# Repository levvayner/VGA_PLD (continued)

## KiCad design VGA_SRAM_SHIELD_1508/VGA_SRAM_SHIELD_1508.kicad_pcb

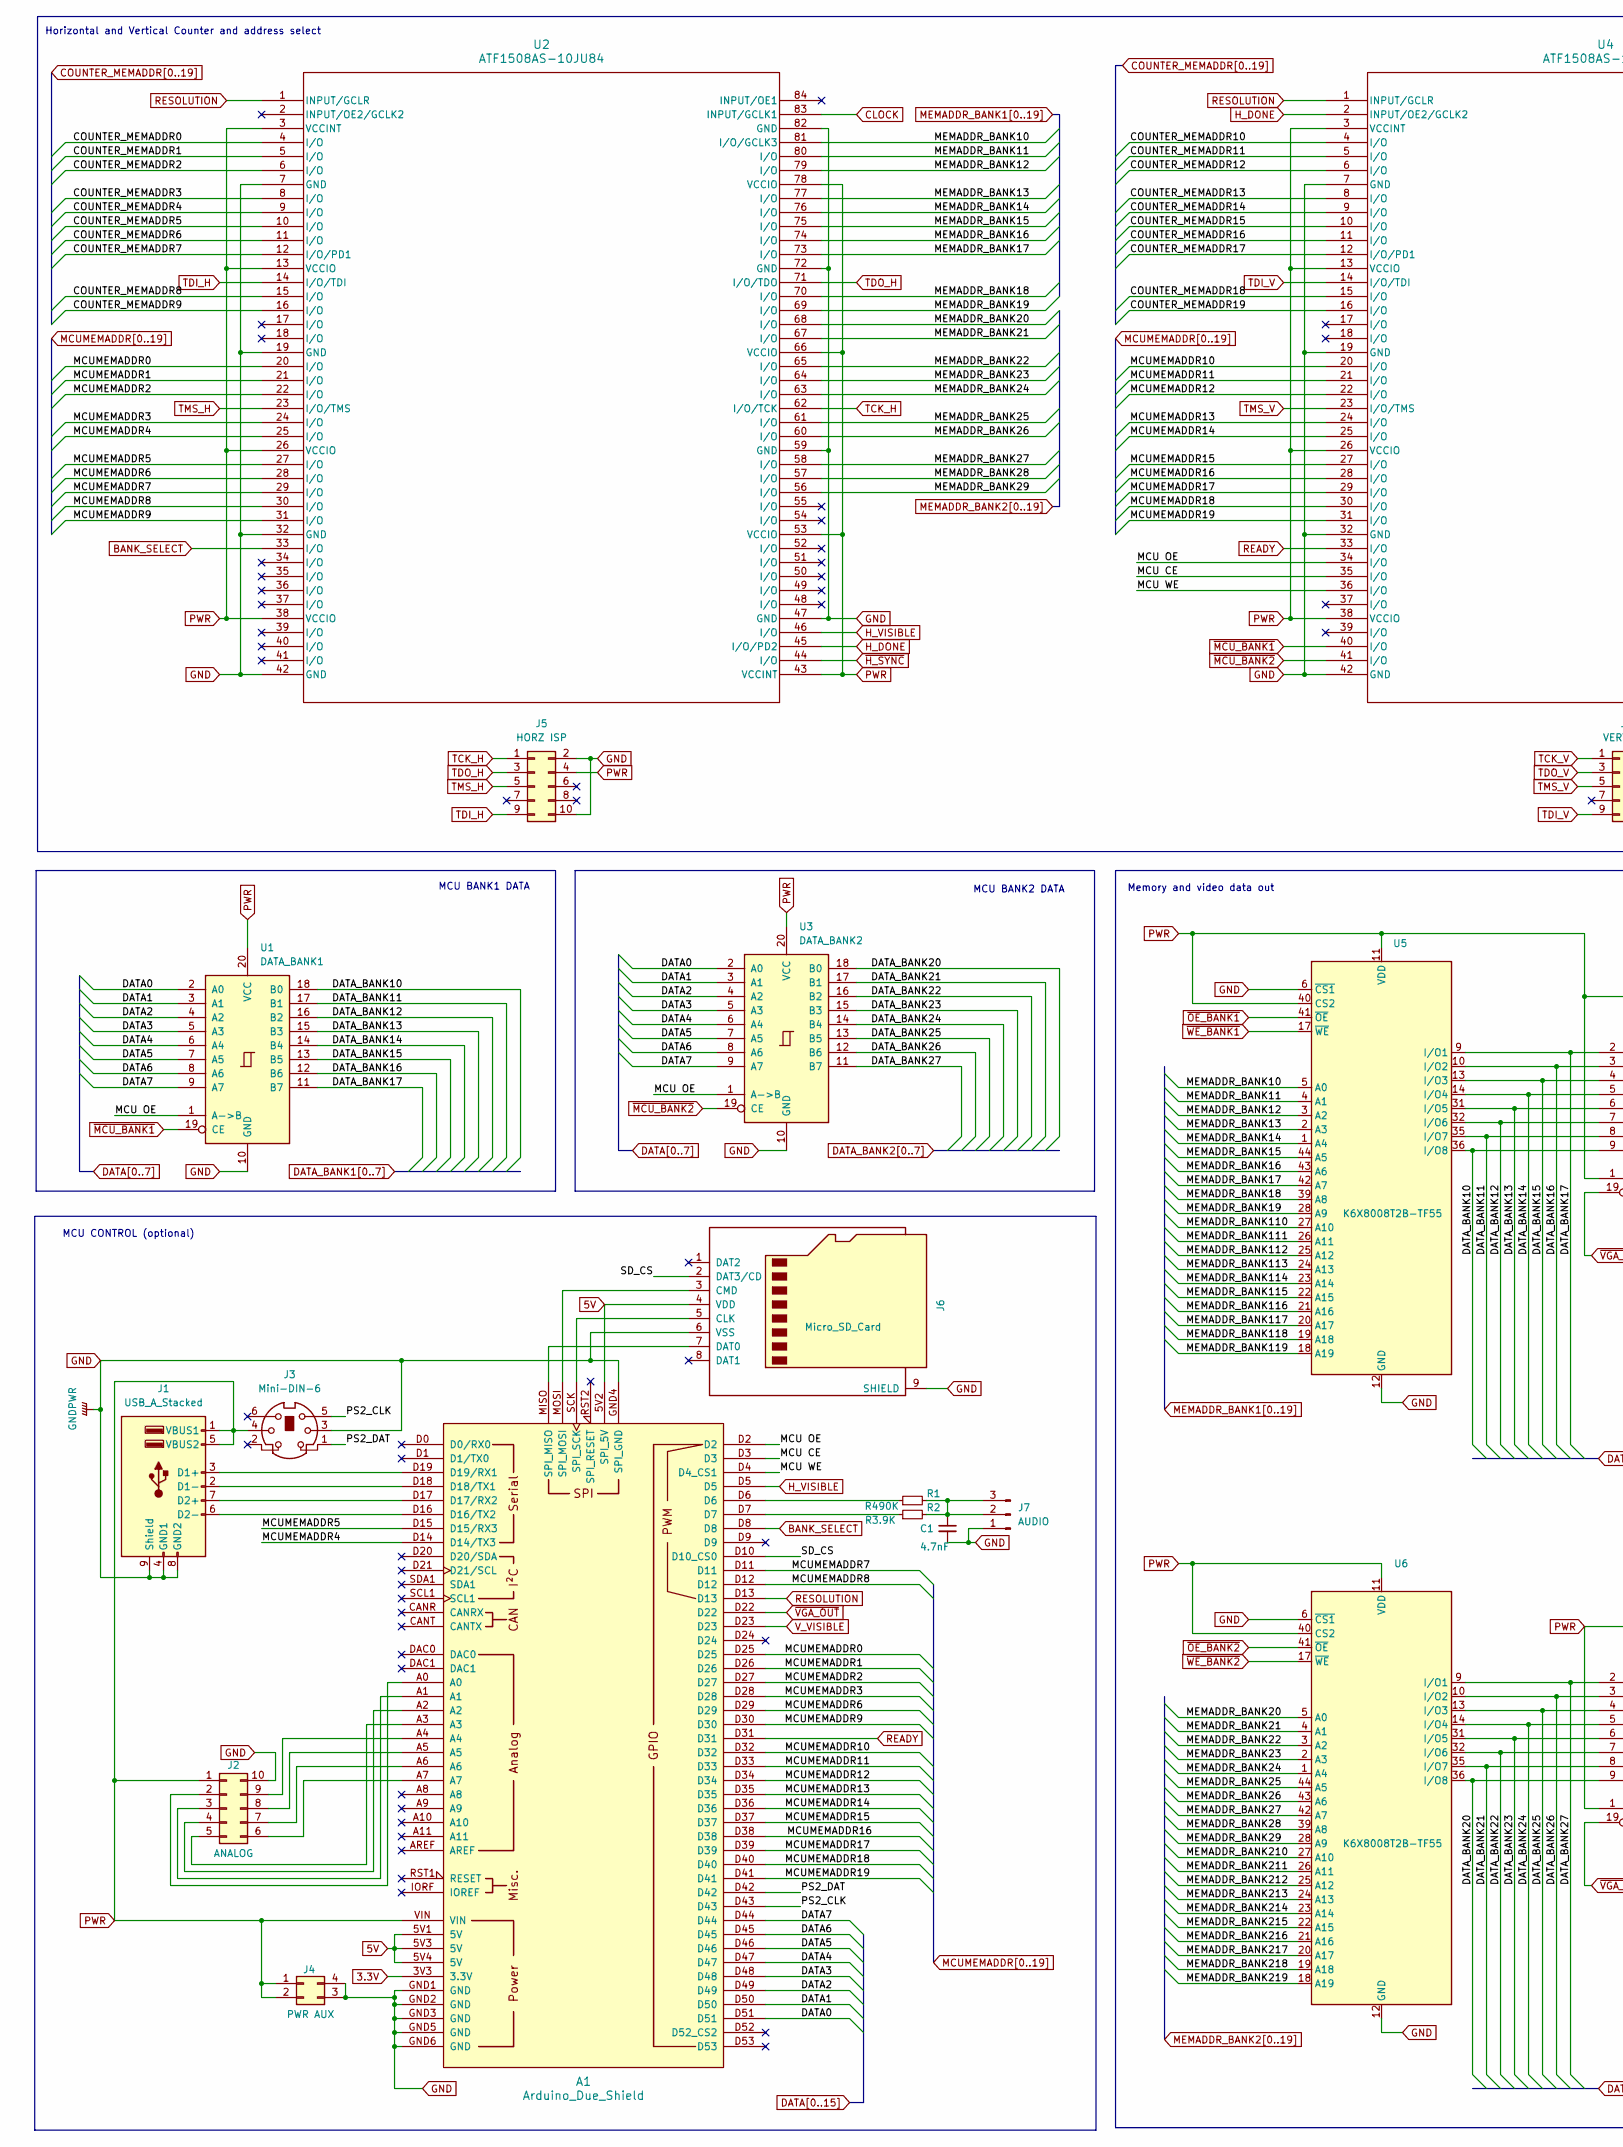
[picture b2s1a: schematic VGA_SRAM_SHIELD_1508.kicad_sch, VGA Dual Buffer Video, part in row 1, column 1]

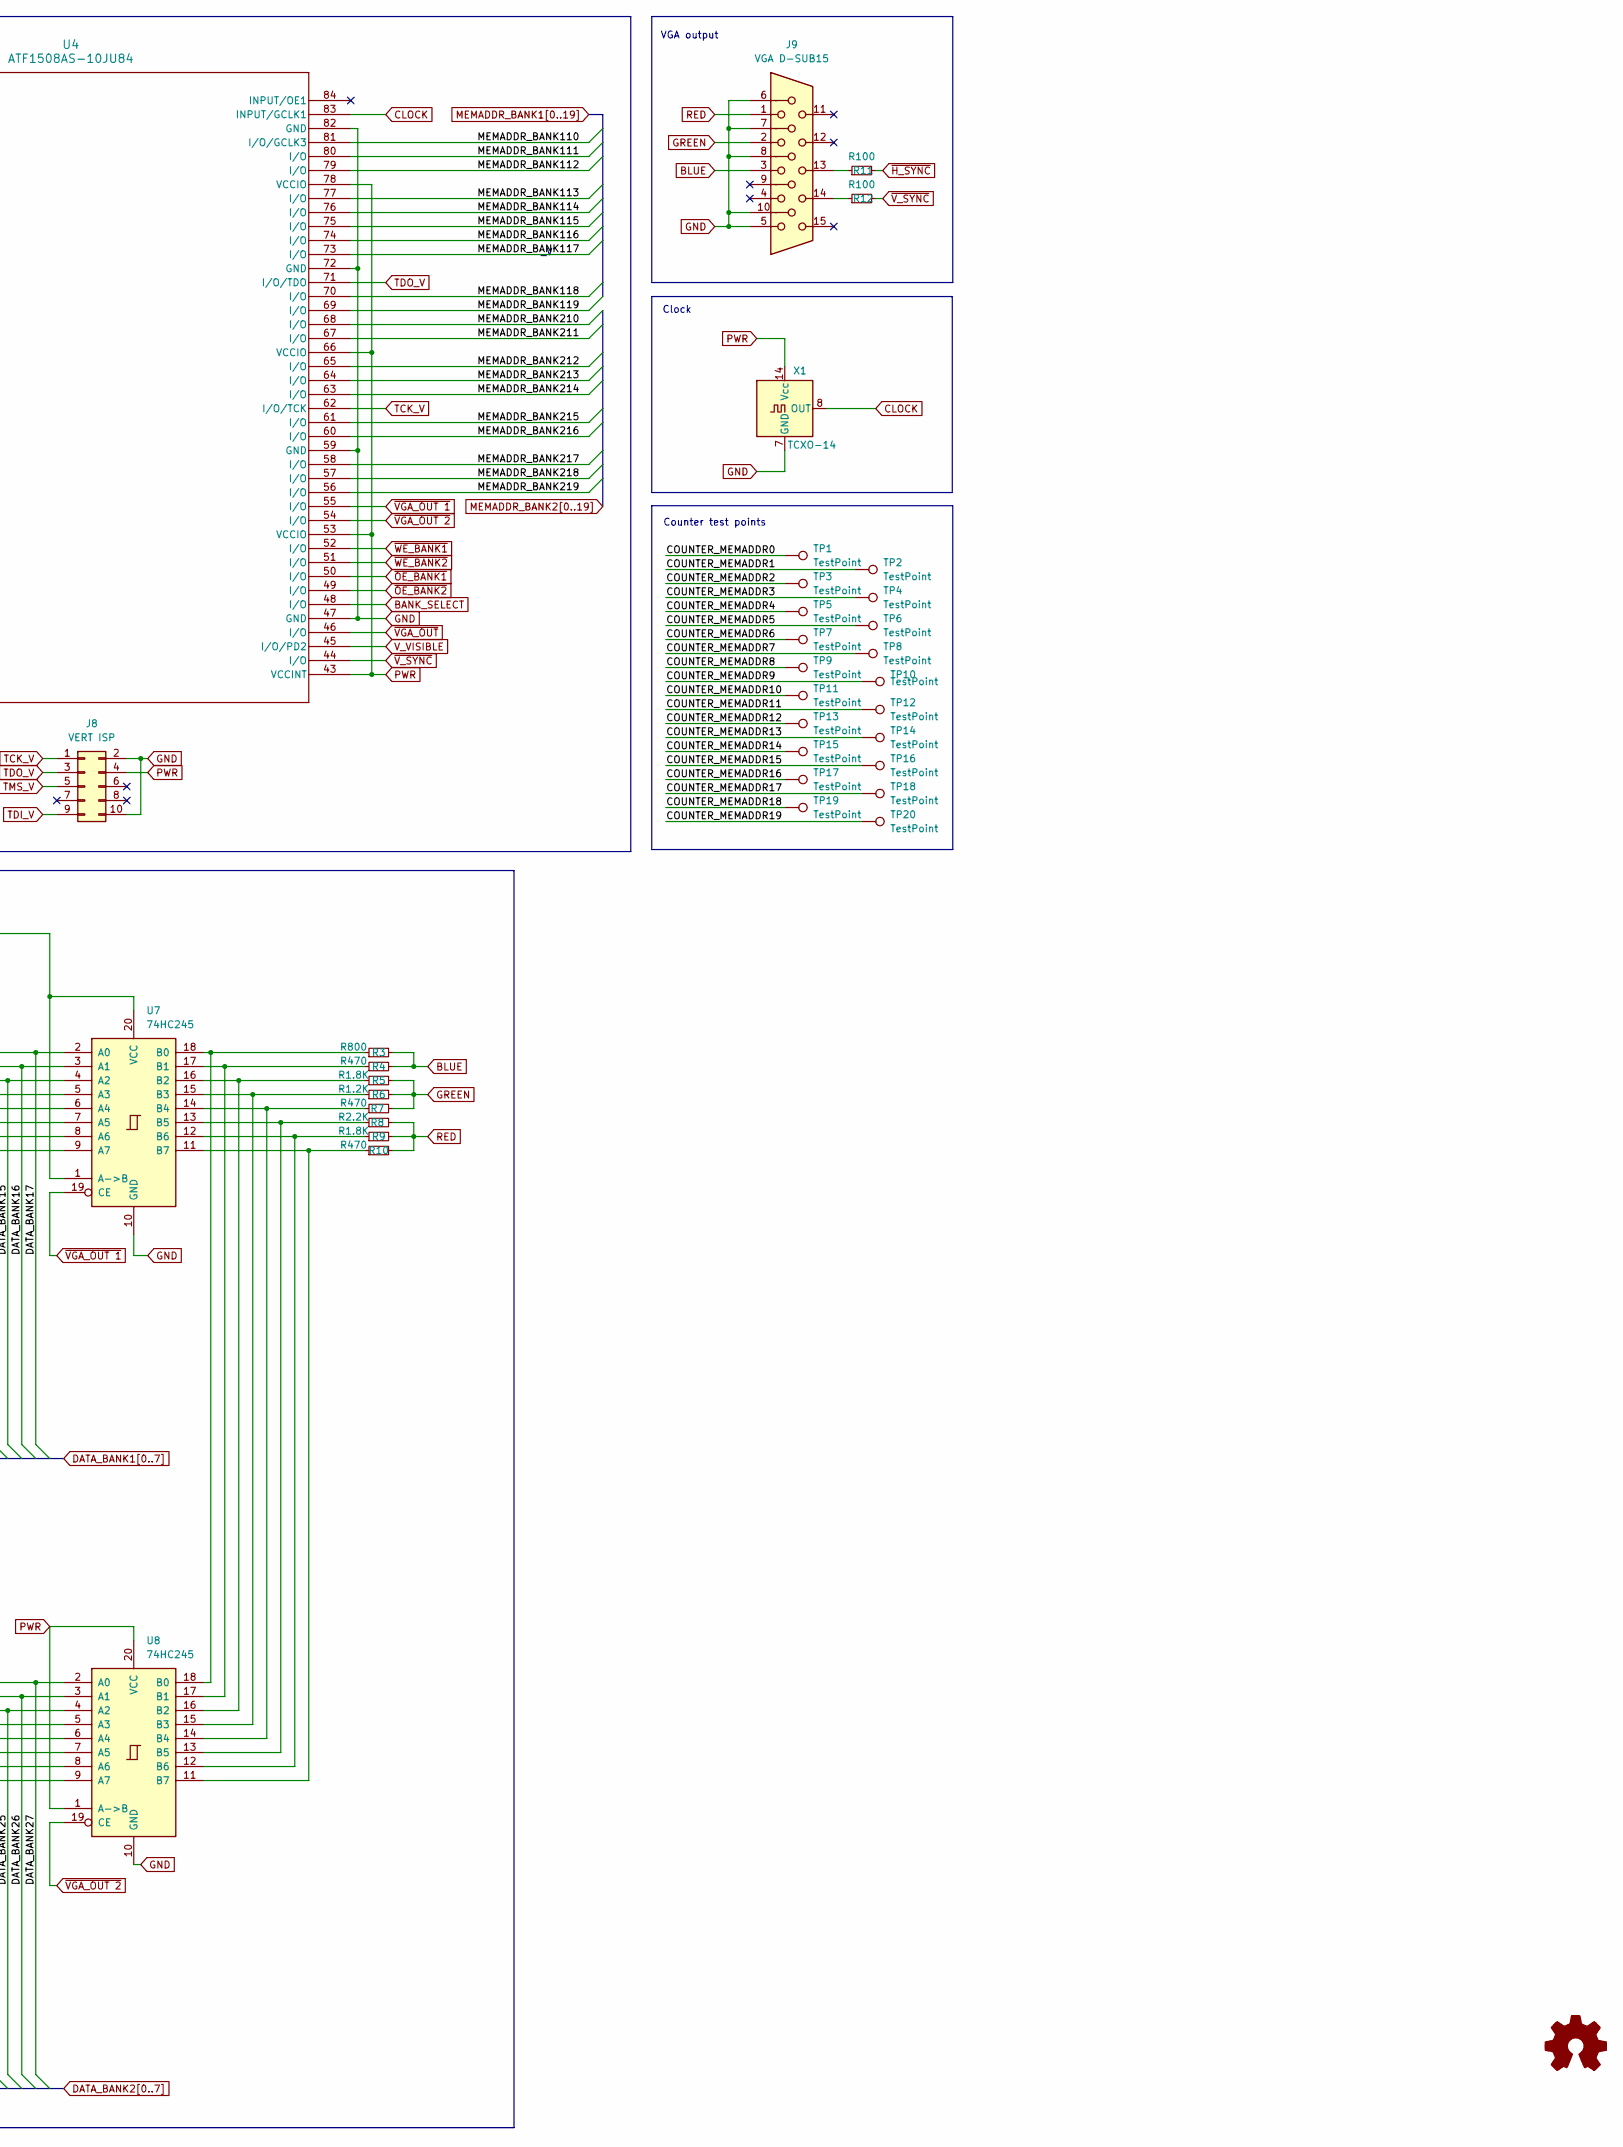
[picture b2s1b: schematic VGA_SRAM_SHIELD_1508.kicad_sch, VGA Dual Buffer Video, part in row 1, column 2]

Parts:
A1: Arduino_Due_Shield
C1: 4.7nF; C_0805_2012Metric
J1: USB_A_Stacked; USB_A_CUI_UJ2-ADH-TH_Horizontal_Stacked
J2: ANALOG; PinSocket_2x05_P2.54mm_Vertical
J3: Mini-DIN-6; mini-DIN 6
J4: PWR AUX; PinSocket_2x02_P2.54mm_Vertical
J5: HORZ ISP; PinSocket_2x05_P2.54mm_Vertical
J6: Micro_SD_Card; J_SD_Card-micro_socket_A
J7: AUDIO; PinSocket_1x03_P2.54mm_Vertical
J8: VERT ISP; PinSocket_2x05_P2.54mm_Vertical
J9: VGA D-SUB15; DSUB-15-HD_Female_Horizontal_P2.29x1.90mm_EdgePinOffset3.03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
R1: R490K; R_0805_2012Metric
R2: R3.9K; R_0805_2012Metric
R3: R800; R_0805_2012Metric
R4, R7, R10: R470; R_0805_2012Metric
R5, R9: R1.8K; R_0805_2012Metric
R6: R1.2K; R_0805_2012Metric
R8: R2.2K; R_0805_2012Metric
R11, R12: R100; R_0805_2012Metric
TP1, TP2, TP3, TP4, TP5, TP6, TP7, TP8, TP9, TP10, TP11, TP12, TP13, TP14, TP15, TP16, TP17, TP18, TP19, TP20: TestPoint; TestPoint_Pad_D1.0mm
U1: DATA_BANK1; SOP-20_7.5x12.8mm_P1.27mm
U2, U4: ATF1508AS-10JU84; PLCC84AT
U3: DATA_BANK2; SOP-20_7.5x12.8mm_P1.27mm
U5, U6: K6X8008T2B-TF55; TSOP-II-44_10.16x18.41mm_P0.8mm
U7, U8: 74HC245; SOP-20_7.5x12.8mm_P1.27mm
X1: TCXO-14; Oscillator_DIP-14

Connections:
3.3V: A1.3V3 (3.3V)
5V: A1.5V1 (5V), A1.5V2 (SPI_5V), A1.5V3 (5V), A1.5V4 (5V), J6.4 (VDD)
/MCU CE: A1.D3, U4.35 (I/O)
/MCU OE: A1.D2, U1.1 (A->B), U3.1 (A->B), U4.34 (I/O)
/MCU WE: A1.D4 (D4_CS1), U4.36 (I/O)
/PS2_CLK: A1.D43, J3.5
/PS2_DAT: A1.D42, J3.1
/SD_CS: A1.D10 (D10_CS0), J6.2 (DAT3/CD)
BANK_SELECT: A1.D8, U2.33 (I/O), U4.48 (I/O)
BLUE: J9.3, R3.2, R4.2
CLOCK: U2.83 (INPUT/GCLK1), U4.83 (INPUT/GCLK1), X1.8 (OUT)
COUNTER_MEMADDR0: TP1.1, U2.4 (I/O)
COUNTER_MEMADDR1: TP2.1, U2.5 (I/O)
COUNTER_MEMADDR2: TP3.1, U2.6 (I/O)
COUNTER_MEMADDR3: TP4.1, U2.8 (I/O)
COUNTER_MEMADDR4: TP5.1, U2.9 (I/O)
COUNTER_MEMADDR5: TP6.1, U2.10 (I/O)
COUNTER_MEMADDR6: TP7.1, U2.11 (I/O)
COUNTER_MEMADDR7: TP8.1, U2.12 (I/O/PD1)
COUNTER_MEMADDR8: TP9.1, U2.15 (I/O)
COUNTER_MEMADDR9: TP10.1, U2.16 (I/O)
COUNTER_MEMADDR10: TP11.1, U4.4 (I/O)
COUNTER_MEMADDR11: TP12.1, U4.5 (I/O)
COUNTER_MEMADDR12: TP13.1, U4.6 (I/O)
COUNTER_MEMADDR13: TP14.1, U4.8 (I/O)
COUNTER_MEMADDR14: TP15.1, U4.9 (I/O)
COUNTER_MEMADDR15: TP16.1, U4.10 (I/O)
COUNTER_MEMADDR16: TP17.1, U4.11 (I/O)
COUNTER_MEMADDR17: TP18.1, U4.12 (I/O/PD1)
COUNTER_MEMADDR18: TP19.1, U4.15 (I/O)
COUNTER_MEMADDR19: TP20.1, U4.16 (I/O)
DATA0: A1.D51, U1.2 (A0), U3.2 (A0)
DATA1: A1.D50, U1.3 (A1), U3.3 (A1)
DATA2: A1.D49, U1.4 (A2), U3.4 (A2)
DATA3: A1.D48, U1.5 (A3), U3.5 (A3)
DATA4: A1.D47, U1.6 (A4), U3.6 (A4)
DATA5: A1.D46, U1.7 (A5), U3.7 (A5)
DATA6: A1.D45, U1.8 (A6), U3.8 (A6)
DATA7: A1.D44, U1.9 (A7), U3.9 (A7)
DATA_BANK10: U1.18 (B0), U5.36 (I/O8), U7.9 (A7)
DATA_BANK11: U1.17 (B1), U5.35 (I/O7), U7.8 (A6)
DATA_BANK12: U1.16 (B2), U5.32 (I/O6), U7.7 (A5)
DATA_BANK13: U1.15 (B3), U5.31 (I/O5), U7.6 (A4)
DATA_BANK14: U1.14 (B4), U5.14 (I/O4), U7.5 (A3)
DATA_BANK15: U1.13 (B5), U5.13 (I/O3), U7.4 (A2)
DATA_BANK16: U1.12 (B6), U5.10 (I/O2), U7.3 (A1)
DATA_BANK17: U1.11 (B7), U5.9 (I/O1), U7.2 (A0)
DATA_BANK20: U3.18 (B0), U6.36 (I/O8), U8.9 (A7)
DATA_BANK21: U3.17 (B1), U6.35 (I/O7), U8.8 (A6)
DATA_BANK22: U3.16 (B2), U6.32 (I/O6), U8.7 (A5)
DATA_BANK23: U3.15 (B3), U6.31 (I/O5), U8.6 (A4)
DATA_BANK24: U3.14 (B4), U6.14 (I/O4), U8.5 (A3)
DATA_BANK25: U3.13 (B5), U6.13 (I/O3), U8.4 (A2)
DATA_BANK26: U3.12 (B6), U6.10 (I/O2), U8.3 (A1)
DATA_BANK27: U3.11 (B7), U6.9 (I/O1), U8.2 (A0)
GND: A1.GND1 (GND), A1.GND2 (GND), A1.GND3 (GND), A1.GND4 (SPI_GND), A1.GND5 (GND), A1.GND6 (GND), C1.2, J1.4 (GND1), J1.8 (GND2), J1.9 (Shield), J2.10, J3.3, J4.3, J4.4, J5.2, J5.10, J6.6 (VSS), J6.9 (SHIELD), J7.1, J8.2, J8.10, J9.5, J9.6, J9.7, J9.8, J9.10, U1.10 (GND), U2.7 (GND), U2.19 (GND), U2.32 (GND), U2.42 (GND), U2.47 (GND), U2.59 (GND), U2.72 (GND), U2.82 (GND), U3.10 (GND), U4.7 (GND), U4.19 (GND), U4.32 (GND), U4.42 (GND), U4.47 (GND), U4.59 (GND), U4.72 (GND), U4.82 (GND), U5.6 (~CS1), U5.12 (GND), U5.34 (GND), U6.6 (~CS1), U6.12 (GND), U6.34 (GND), U7.10 (GND), U8.10 (GND), X1.7 (GND)
GREEN: J9.2, R5.2, R6.2, R7.2
H_DONE: U2.45 (I/O/PD2), U4.2 (INPUT/OE2/GCLK2)
H_VISIBLE: A1.D5, U2.46 (I/O)
MCUMEMADDR0: A1.D25, U2.20 (I/O)
MCUMEMADDR1: A1.D26, U2.21 (I/O)
MCUMEMADDR2: A1.D27, U2.22 (I/O)
MCUMEMADDR3: A1.D28, U2.24 (I/O)
MCUMEMADDR4: A1.D14 (D14/TX3), U2.25 (I/O)
MCUMEMADDR5: A1.D15 (D15/RX3), U2.27 (I/O)
MCUMEMADDR6: A1.D29, U2.28 (I/O)
MCUMEMADDR7: A1.D11, U2.29 (I/O)
MCUMEMADDR8: A1.D12, U2.30 (I/O)
MCUMEMADDR9: A1.D30, U2.31 (I/O)
MCUMEMADDR10: A1.D32, U4.20 (I/O)
MCUMEMADDR11: A1.D33, U4.21 (I/O)
MCUMEMADDR12: A1.D34, U4.22 (I/O)
MCUMEMADDR13: A1.D35, U4.24 (I/O)
MCUMEMADDR14: A1.D36, U4.25 (I/O)
MCUMEMADDR15: A1.D37, U4.27 (I/O)
MCUMEMADDR16: A1.D38, U4.28 (I/O)
MCUMEMADDR17: A1.D39, U4.29 (I/O)
MCUMEMADDR18: A1.D40, U4.30 (I/O)
MCUMEMADDR19: A1.D41, U4.31 (I/O)
MEMADDR_BANK10: U2.81 (I/O/GCLK3), U5.5 (A0)
MEMADDR_BANK11: U2.80 (I/O), U5.4 (A1)
MEMADDR_BANK12: U2.79 (I/O), U5.3 (A2)
MEMADDR_BANK13: U2.77 (I/O), U5.2 (A3)
MEMADDR_BANK14: U2.76 (I/O), U5.1 (A4)
MEMADDR_BANK15: U2.75 (I/O), U5.44 (A5)
MEMADDR_BANK16: U2.74 (I/O), U5.43 (A6)
MEMADDR_BANK17: U2.73 (I/O), U5.42 (A7)
MEMADDR_BANK18: U2.70 (I/O), U5.39 (A8)
MEMADDR_BANK19: U2.69 (I/O), U5.28 (A9)
MEMADDR_BANK20: U2.68 (I/O), U6.5 (A0)
MEMADDR_BANK21: U2.67 (I/O), U6.4 (A1)
MEMADDR_BANK22: U2.65 (I/O), U6.3 (A2)
MEMADDR_BANK23: U2.64 (I/O), U6.2 (A3)
MEMADDR_BANK24: U2.63 (I/O), U6.1 (A4)
MEMADDR_BANK25: U2.61 (I/O), U6.44 (A5)
MEMADDR_BANK26: U2.60 (I/O), U6.43 (A6)
MEMADDR_BANK27: U2.58 (I/O), U6.42 (A7)
MEMADDR_BANK28: U2.57 (I/O), U6.39 (A8)
MEMADDR_BANK29: U2.56 (I/O), U6.28 (A9)
MEMADDR_BANK110: U4.81 (I/O/GCLK3), U5.27 (A10)
MEMADDR_BANK111: U4.80 (I/O), U5.26 (A11)
MEMADDR_BANK112: U4.79 (I/O), U5.25 (A12)
MEMADDR_BANK113: U4.77 (I/O), U5.24 (A13)
MEMADDR_BANK114: U4.76 (I/O), U5.23 (A14)
MEMADDR_BANK115: U4.75 (I/O), U5.22 (A15)
MEMADDR_BANK116: U4.74 (I/O), U5.21 (A16)
MEMADDR_BANK117: U4.73 (I/O), U5.20 (A17)
MEMADDR_BANK118: U4.70 (I/O), U5.19 (A18)
MEMADDR_BANK119: U4.69 (I/O), U5.18 (A19)
MEMADDR_BANK210: U4.68 (I/O), U6.27 (A10)
MEMADDR_BANK211: U4.67 (I/O), U6.26 (A11)
MEMADDR_BANK212: U4.65 (I/O), U6.25 (A12)
MEMADDR_BANK213: U4.64 (I/O), U6.24 (A13)
MEMADDR_BANK214: U4.63 (I/O), U6.23 (A14)
MEMADDR_BANK215: U4.61 (I/O), U6.22 (A15)
MEMADDR_BANK216: U4.60 (I/O), U6.21 (A16)
MEMADDR_BANK217: U4.58 (I/O), U6.20 (A17)
MEMADDR_BANK218: U4.57 (I/O), U6.19 (A18)
MEMADDR_BANK219: U4.56 (I/O), U6.18 (A19)
unnamed: A1.D16 (D16/TX2), J1.6 (D2-)
unnamed: A1.D17 (D17/RX2), J1.7 (D2+)
unnamed: A1.D18 (D18/TX1), J1.2 (D1-)
unnamed: A1.D19 (D19/RX1), J1.3 (D1+)
unnamed: A1.D6, R1.1
unnamed: A1.D7, R2.1
unnamed: A1.MISO (SPI_MISO), J6.7 (DAT0)
unnamed: A1.MOSI (SPI_MOSI), J6.3 (CMD)
unnamed: A1.SCK (SPI_SCK), J6.5 (CLK)
unnamed: A1.A0, J2.2
unnamed: A1.A1, J2.3
unnamed: A1.A2, J2.4
unnamed: A1.A3, J2.5
unnamed: A1.A7, J2.6
unnamed: A1.A6, J2.7
unnamed: A1.A5, J2.8
unnamed: A1.A4, J2.9
unnamed: C1.1, J7.2, J7.3, R1.2, R2.2
unnamed: J9.13, R11.1
unnamed: J9.14, R12.1
unnamed: R3.1, U7.18 (B0), U8.18 (B0)
unnamed: R4.1, U7.17 (B1), U8.17 (B1)
unnamed: R5.1, U7.16 (B2), U8.16 (B2)
unnamed: R6.1, U7.15 (B3), U8.15 (B3)
unnamed: R7.1, U7.14 (B4), U8.14 (B4)
unnamed: R8.1, U7.13 (B5), U8.13 (B5)
unnamed: R9.1, U7.12 (B6), U8.12 (B6)
unnamed: R10.1, U7.11 (B7), U8.11 (B7)
PWR: A1.VIN, J1.1 (VBUS1), J1.5 (VBUS2), J2.1, J3.4, J4.1, J4.2, J5.4, J8.4, U1.20 (VCC), U2.3 (VCCINT), U2.13 (VCCIO), U2.26 (VCCIO), U2.38 (VCCIO), U2.43 (VCCINT), U2.53 (VCCIO), U2.66 (VCCIO), U2.78 (VCCIO), U3.20 (VCC), U4.3 (VCCINT), U4.13 (VCCIO), U4.26 (VCCIO), U4.38 (VCCIO), U4.43 (VCCINT), U4.53 (VCCIO), U4.66 (VCCIO), U4.78 (VCCIO), U5.11 (VDD), U5.33 (VDD), U5.40 (CS2), U6.11 (VDD), U6.33 (VDD), U6.40 (CS2), U7.1 (A->B), U7.20 (VCC), U8.1 (A->B), U8.20 (VCC), X1.14 (Vcc)
READY: A1.D31, U4.33 (I/O)
RED: J9.1, R8.2, R9.2, R10.2
RESOLUTION: A1.D13, U2.1 (INPUT/GCLR), U4.1 (INPUT/GCLR)
TCK_H: J5.1, U2.62 (I/O/TCK)
TCK_V: J8.1, U4.62 (I/O/TCK)
TDI_H: J5.9, U2.14 (I/O/TDI)
TDI_V: J8.9, U4.14 (I/O/TDI)
TDO_H: J5.3, U2.71 (I/O/TDO)
TDO_V: J8.3, U4.71 (I/O/TDO)
TMS_H: J5.5, U2.23 (I/O/TMS)
TMS_V: J8.5, U4.23 (I/O/TMS)
V_VISIBLE: A1.D23, U4.45 (I/O/PD2)
~H_SYNC: R11.2, U2.44 (I/O)
~MCU_BANK1: U1.19 (CE), U4.40 (I/O)
~MCU_BANK2: U3.19 (CE), U4.41 (I/O)
~OE_BANK1: U4.50 (I/O), U5.41 (~OE)
~OE_BANK2: U4.49 (I/O), U6.41 (~OE)
~VGA_OUT 1: U4.55 (I/O), U7.19 (CE)
~VGA_OUT 2: U4.54 (I/O), U8.19 (CE)
~VGA_OUT: A1.D22, U4.46 (I/O)
~V_SYNC: R12.2, U4.44 (I/O)
~WE_BANK1: U4.52 (I/O), U5.17 (~WE)
~WE_BANK2: U4.51 (I/O), U6.17 (~WE)

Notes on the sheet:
Horizontal and Vertical Counter and address select
Memory and video data out
Clock
Counter test points
MCU BANK1 DATA
MCU BANK2 DATA
MCU CONTROL (optional)
VGA output

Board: 4 copper layers, 52 parts (4 on the bottom side), 170 nets, no tracks yet.

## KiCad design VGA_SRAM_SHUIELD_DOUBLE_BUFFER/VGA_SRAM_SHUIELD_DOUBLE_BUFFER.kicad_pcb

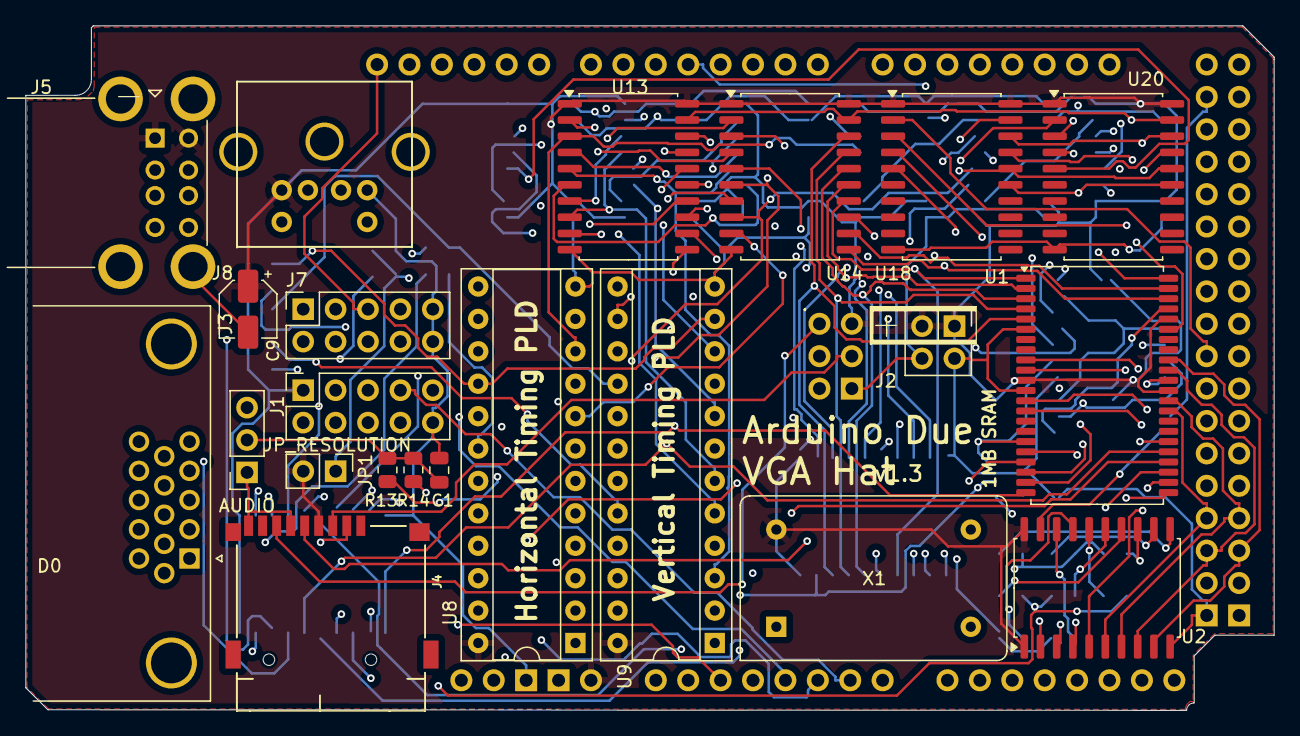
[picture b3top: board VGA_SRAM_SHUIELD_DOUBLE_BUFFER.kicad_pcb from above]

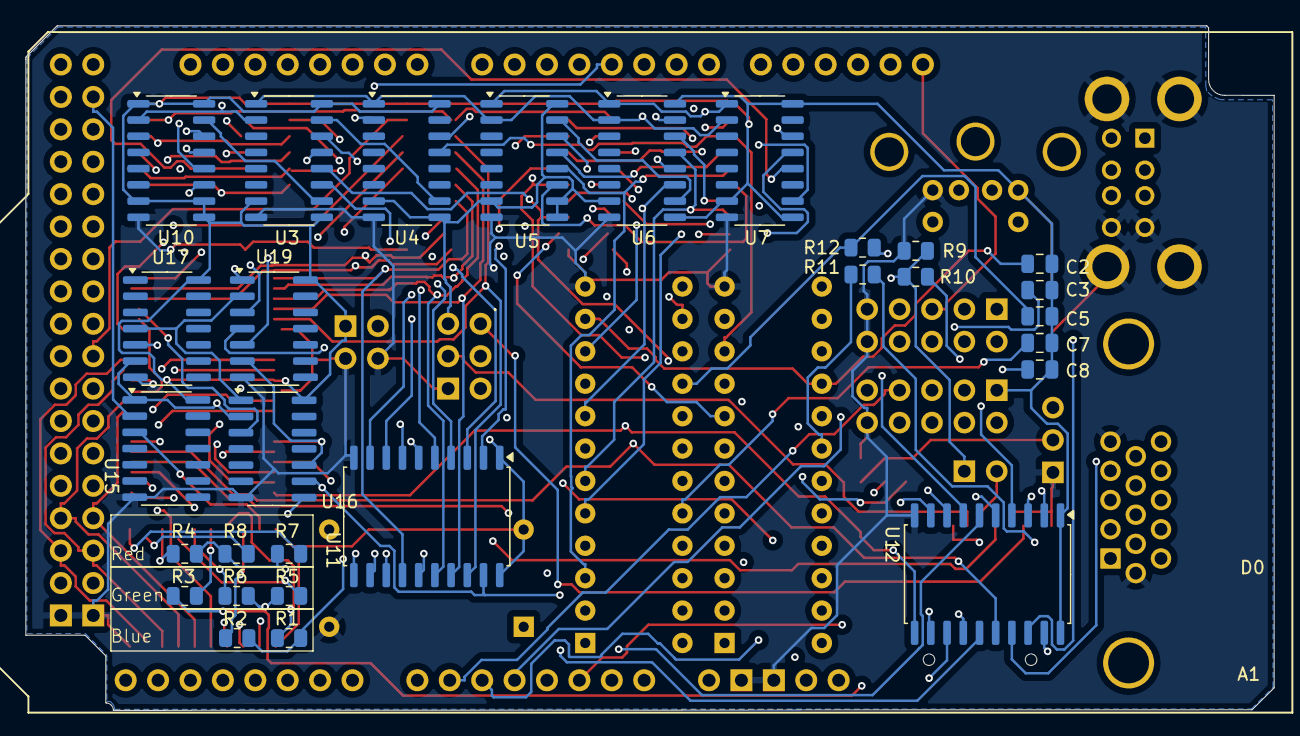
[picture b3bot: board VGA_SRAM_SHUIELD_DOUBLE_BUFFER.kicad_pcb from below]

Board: 4 copper layers, 97.8 x 53.7 mm, 52 parts (29 on the bottom side), 135 nets.

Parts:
A1: Arduino_Due_Shield
C1: 4.7nF; C_0805_2012Metric
C2, C3, C5, C7, C8: 560pf; C_0805_2012Metric
C9: C_Small; CP_Elec_4x4.5
J1: ANALOG; PinSocket_2x05_P2.54mm_Vertical
J2: PWR AUX; PinSocket_2x02_P2.54mm_Vertical
J3: DE15_Receptacle_HighDensity; DSUB-15-HD_Female_Horizontal_P2.29x1.98mm_EdgePinOffset8.35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
J4: Micro_SD_Card; J_SD_Card-micro_socket_A
J5: USB_A_Stacked; USB_A_CUI_UJ2-ADH-TH_Horizontal_Stacked
J6: AUDIO; PinSocket_1x03_P2.54mm_Vertical
J7: DIGITAL; PinSocket_2x05_P2.54mm_Vertical
J8: Mini-DIN-6; mini-DIN 6
JP1: JP_RESOLUTION; PinHeader_1x02_P2.54mm_Vertical
R1, R5, R7: R470; R_0805_2012Metric
R2: R800; R_0805_2012Metric
R3, R8: R1.8K; R_0805_2012Metric
R4: R2.2K; R_0805_2012Metric
R6: R1.2K; R_0805_2012Metric
R9: 10K; R_0805_2012Metric
R10: R200; R_0805_2012Metric
R11, R12: R100; R_0805_2012Metric
R13: R490K; R_0805_2012Metric
R14: R3.9K; R_0805_2012Metric
U1: K6X8008T2B-TF55; TSOP-II-44_10.16x18.41mm_P0.8mm
U2, U11, U12, U13, U14, U18, U20: 74HC245; SOP-20_7.5x12.8mm_P1.27mm
U3, U4, U5, U6, U7, U10: 74LS161; SO-16_3.9x9.9mm_P1.27mm
U8, U9: GAL22V10; DIP-24_W7.62mm_Socket
U15: 74LS32; SO-14_3.9x8.65mm_P1.27mm
U16: 74LS08; SO-14_3.9x8.65mm_P1.27mm
U17: 74HC00; SO-14_3.9x8.65mm_P1.27mm
U19: 74HC14; SO-14_3.9x8.65mm_P1.27mm
X1: TCXO-14; Oscillator_DIP-14

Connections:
3.3V: A1.3V3 (3.3V), J7.2
5V: A1.5V1 (5V), A1.5V3 (5V), A1.5V4 (5V), J7.1
/MCU CE: A1.D3, U19.3
/MCU OE: A1.D2, U19.1
/MCU WE: A1.D4 (D4_CS1), U19.5
A0: U8.1 (I1), U10.14 (Q0), U14.2 (A0)
A1: U8.2 (I2), U10.13 (Q1), U14.3 (A1)
A2: U8.3 (I3), U10.12 (Q2), U14.4 (A2)
A3: U8.4 (I4), U10.11 (Q3), U14.5 (A3)
A4: U3.14 (Q0), U8.5 (I5), U14.6 (A4)
A5: U3.13 (Q1), U8.6 (I6), U14.7 (A5)
A6: U3.12 (Q2), U8.7 (I7), U14.8 (A6)
A7: U3.11 (Q3), U8.8 (I8), U14.9 (A7)
A8: U4.14 (Q0), U8.9 (I9), U13.2 (A0)
A9: U4.13 (Q1), U8.10 (I10), U13.3 (A1)
A10: U5.13 (Q1), U9.2 (I2), U13.4 (A2)
A11: U5.12 (Q2), U9.3 (I3), U13.5 (A3)
A12: U5.11 (Q3), U9.4 (I4), U13.6 (A4)
A13: U6.14 (Q0), U9.5 (I5), U13.7 (A5)
A14: U6.13 (Q1), U9.6 (I6), U13.8 (A6)
A15: U6.12 (Q2), U9.7 (I7), U13.9 (A7)
A16: U6.11 (Q3), U9.8 (I8), U20.2 (A0)
A17: U7.14 (Q0), U9.9 (I9), U20.3 (A1)
A18: U7.13 (Q1), U9.10 (I10), U20.4 (A2)
A19: U7.12 (Q2), U20.5 (A3)
D8: A1.D8, J7.3
D9: A1.D9, J7.4
D13: A1.D13, J7.5
D31: A1.D31, J7.6
D42: A1.D42, J7.7
D43: A1.D43, J7.8
DATA0: A1.D51, U1.36 (I/O8), U2.9 (A7)
DATA1: A1.D50, U1.35 (I/O7), U2.8 (A6)
DATA2: A1.D49, U1.32 (I/O6), U2.7 (A5)
DATA3: A1.D48, U1.31 (I/O5), U2.6 (A4)
DATA4: A1.D47, U1.14 (I/O4), U2.5 (A3)
DATA5: A1.D46, U1.13 (I/O3), U2.4 (A2)
DATA6: A1.D45, U1.10 (I/O2), U2.3 (A1)
DATA7: A1.D44, U1.9 (I/O1), U2.2 (A0)
GND: A1.GND2 (GND), A1.GND3 (GND), A1.GND4 (SPI_GND), A1.GND5 (GND), A1.GND6 (GND), C1.2, C9.2, J1.10, J2.3, J2.4, J3.5, J3.6, J3.7, J3.8, J3.10, J4.6 (VSS), J4.9 (SHIELD), J5.4 (GND1), J5.8 (GND2), J5.9 (Shield), J6.1, J7.9, J7.10, J8.3, R9.1, U1.6 (~CS1), U1.12 (GND), U1.34 (GND), U2.10 (GND), U3.8 (GND), U4.8 (GND), U5.8 (GND), U6.8 (GND), U7.8 (GND), U8.12 (GND), U9.12 (GND), U10.8 (GND), U11.10 (GND), U12.10 (GND), U13.10 (GND), U14.10 (GND), U15.7 (GND), U16.7 (GND), U17.7 (GND), U18.10 (GND), U19.7 (GND), U20.10 (GND), X1.7 (GND)
H_CLK: U3.2 (CP), U4.2 (CP), U10.2 (CP), X1.8 (OUT)
H_VISIBLE: A1.D24, C2.2, U8.16 (IO16), U9.11 (I11)
MCUMEMADDR0: A1.D25, U11.2 (A0)
MCUMEMADDR1: A1.D26, U11.3 (A1)
MCUMEMADDR2: A1.D27, U11.4 (A2)
MCUMEMADDR3: A1.D28, U11.5 (A3)
MCUMEMADDR4: A1.D14 (D14/TX3), U11.6 (A4)
MCUMEMADDR5: A1.D15 (D15/RX3), U11.7 (A5)
MCUMEMADDR6: A1.D29, U11.8 (A6)
MCUMEMADDR7: A1.D11, U11.9 (A7)
MCUMEMADDR8: A1.D12, U12.2 (A0)
MCUMEMADDR9: A1.D30, U12.3 (A1)
MCUMEMADDR10: A1.D32, U12.4 (A2)
MCUMEMADDR11: A1.D33, U12.5 (A3)
MCUMEMADDR12: A1.D34, U12.6 (A4)
MCUMEMADDR13: A1.D35, U12.7 (A5)
MCUMEMADDR14: A1.D36, U12.8 (A6)
MCUMEMADDR15: A1.D37, U12.9 (A7)
MCUMEMADDR16: A1.D38, U18.2 (A0)
MCUMEMADDR17: A1.D39, U18.3 (A1)
MCUMEMADDR18: A1.D40, U18.4 (A2)
MCUMEMADDR19: A1.D41, U18.5 (A3)
MEMADDR0: U1.5 (A0), U11.18 (B0), U14.18 (B0)
MEMADDR1: U1.4 (A1), U11.17 (B1), U14.17 (B1)
MEMADDR2: U1.3 (A2), U11.16 (B2), U14.16 (B2)
MEMADDR3: U1.2 (A3), U11.15 (B3), U14.15 (B3)
MEMADDR4: U1.1 (A4), U11.14 (B4), U14.14 (B4)
MEMADDR5: U1.44 (A5), U11.13 (B5), U14.13 (B5)
MEMADDR6: U1.43 (A6), U11.12 (B6), U14.12 (B6)
MEMADDR7: U1.42 (A7), U11.11 (B7), U14.11 (B7)
MEMADDR8: U1.39 (A8), U12.18 (B0), U13.18 (B0)
MEMADDR9: U1.28 (A9), U12.17 (B1), U13.17 (B1)
MEMADDR10: U1.27 (A10), U12.16 (B2), U13.16 (B2)
MEMADDR11: U1.26 (A11), U12.15 (B3), U13.15 (B3)
MEMADDR12: U1.25 (A12), U12.14 (B4), U13.14 (B4)
MEMADDR13: U1.24 (A13), U12.13 (B5), U13.13 (B5)
MEMADDR14: U1.23 (A14), U12.12 (B6), U13.12 (B6)
MEMADDR15: U1.22 (A15), U12.11 (B7), U13.11 (B7)
MEMADDR16: U1.21 (A16), U18.18 (B0), U20.18 (B0)
MEMADDR17: U1.20 (A17), U18.17 (B1), U20.17 (B1)
MEMADDR18: U1.19 (A18), U18.16 (B2), U20.16 (B2)
MEMADDR19: U1.18 (A19), U18.15 (B3), U20.15 (B3)
unnamed: A1.D16 (D16/TX2), J5.6 (D2-), J8.5
unnamed: A1.D17 (D17/RX2), J5.7 (D2+), J8.1
unnamed: A1.D18 (D18/TX1), J5.2 (D1-)
unnamed: A1.D19 (D19/RX1), J5.3 (D1+)
unnamed: A1.D6, R13.1
unnamed: A1.D7, R14.1
unnamed: A1.MISO (SPI_MISO), J4.7 (DAT0)
unnamed: A1.MOSI (SPI_MOSI), J4.3 (CMD)
unnamed: A1.SCK (SPI_SCK), J4.5 (CLK)
unnamed: A1.A0, J1.2
unnamed: A1.A1, J1.3
unnamed: A1.A2, J1.4
unnamed: A1.A3, J1.5
unnamed: A1.A7, J1.6
unnamed: A1.A6, J1.7
unnamed: A1.A5, J1.8
unnamed: A1.A4, J1.9
unnamed: J3.1, R4.2, R7.2, R8.2
unnamed: J3.2, R3.2, R5.2, R6.2
unnamed: J3.3, R1.2, R2.2
unnamed: J3.13, R11.1
unnamed: J3.14, R12.1
unnamed: C1.1, J6.2, J6.3, R13.2, R14.2
unnamed: U1.17 (~WE), U16.10, U19.6
unnamed: R2.1, U2.18 (B0)
unnamed: R1.1, U2.17 (B1)
unnamed: R3.1, U2.16 (B2)
unnamed: R6.1, U2.15 (B3)
unnamed: R5.1, U2.14 (B4)
unnamed: R4.1, U2.13 (B5)
unnamed: R8.1, U2.12 (B6)
unnamed: R7.1, U2.11 (B7)
unnamed: U3.15 (TC), U4.10 (CET)
unnamed: U3.1 (~MR), U4.1 (~MR), U5.2 (CP), U6.2 (CP), U7.2 (CP), U8.20 (IO20)
unnamed: U5.14 (Q0), U9.1 (I1)
unnamed: U5.15 (TC), U6.10 (CET)
unnamed: U6.15 (TC), U7.10 (CET)
unnamed: R10.2, U8.23 (IO23), U9.23 (IO23)
unnamed: U3.10 (CET), U10.15 (TC)
unnamed: U11.19 (CE), U12.19 (CE), U16.9, U18.19 (CE), U19.4
unnamed: U16.8, U17.5
PWR: A1.5V2 (SPI_5V), A1.VIN, C2.1, C3.1, C5.1, C7.1, C8.1, C9.1, J1.1, J2.1, J2.2, J4.4 (VDD), J5.1 (VBUS1), J5.5 (VBUS2), J8.4, JP1.2 (B), U1.11 (VDD), U1.33 (VDD), U1.40 (CS2), U2.1 (A->B), U2.20 (VCC), U3.7 (CEP), U3.9 (~PE), U3.16 (VCC), U4.7 (CEP), U4.9 (~PE), U4.16 (VCC), U5.7 (CEP), U5.9 (~PE), U5.10 (CET), U5.16 (VCC), U6.7 (CEP), U6.9 (~PE), U6.16 (VCC), U7.7 (CEP), U7.9 (~PE), U7.16 (VCC), U8.24 (VCC), U9.24 (VCC), U10.1 (~MR), U10.7 (CEP), U10.9 (~PE), U10.10 (CET), U10.16 (VCC), U11.1 (A->B), U11.20 (VCC), U12.1 (A->B), U12.20 (VCC), U13.1 (A->B), U13.20 (VCC), U14.1 (A->B), U14.20 (VCC), U15.14 (VCC), U16.14 (VCC), U17.14 (VCC), U18.1 (A->B), U18.20 (VCC), U19.14 (VCC), U20.1 (A->B), U20.20 (VCC), X1.14 (Vcc)
RESOLUTION: A1.D5, JP1.1 (A), R9.2, R10.1
SD_CS: A1.D10 (D10_CS0), J4.2 (DAT3/CD)
~H_SYNC: C3.2, R11.2, U8.18 (IO18)
~MCU OE: U16.1, U17.4, U19.2
~OE: U1.41 (~OE), U16.3
~SCREEN_VISIBLE: A1.D22, C8.2, U9.21 (IO21), U15.2
~TIMING ADDR: U13.19 (CE), U14.19 (CE), U15.1, U16.2, U17.6, U20.19 (CE)
~VGA_OUT: U2.19 (CE), U15.3
~V_RESET: C7.2, U5.1 (~MR), U6.1 (~MR), U7.1 (~MR), U9.20 (IO20)
~V_SYNC: C5.2, R12.2, U9.16 (IO16)
~V_VISIBLE: A1.D23, U9.14 (IO14)

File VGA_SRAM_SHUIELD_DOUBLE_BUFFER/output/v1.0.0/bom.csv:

"Reference","Value","Datasheet","Footprint","Qty","DNP"
"A1","Arduino_Due_Shield","https://docs.arduino.cc/hardware/due","arduino-library:Arduino_Due_Shield","1",""
"C1,C2,C3,C4,C5,C7,C8","560pf","~","Capacitor_SMD:C_0805_2012Metric","7",""
"C6,C9","C_Small","~","Capacitor_Tantalum_SMD:CP_EIA-7132-28_AVX-C","2",""
"J1","DIAG","~","Connector_PinSocket_2.54mm:PinSocket_2x04_P2.54mm_Vertical","1",""
"J2","PWR AUX","~","Connector_PinSocket_2.54mm:PinSocket_2x02_P2.54mm_Vertical","1",""
"J3","DE15_Receptacle_HighDensity","~","Connector_Dsub:DSUB-15-HD_Female_Horizontal_P2.29x1.98mm_EdgePinOffset8.35mm_Housed_MountingHolesOffset10.89mm","1",""
"J5","USB_A","~","Connector_USB:USB_A_Molex_67643_Horizontal","1",""
"R1,R4,R7","R470","~","Resistor_SMD:R_0805_2012Metric","3",""
"R2,R5,R8","R900","~","Resistor_SMD:R_0805_2012Metric","3",""
"R3,R6","R1.5K","~","Resistor_SMD:R_0805_2012Metric","2",""
"R10","R10K","~","Resistor_SMD:R_0805_2012Metric","1",""
"R11,R12","R100","~","Resistor_SMD:R_0805_2012Metric","2",""
"U1","K6X8008T2B-TF55","https://www.alldatasheet.com/datasheet-pdf/download/85484/SA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","Package_SO:TSOP-II-44_10.16x18.41mm_P0.8mm","1",""
"U2,U11,U12,U13,U14,U18,U20","74HC245","http://www.ti.com/lit/gpn/sn74HC245","Package_SO:SOP-20_7.5x12.8mm_P1.27mm","7",""
"U3,U4,U5,U6,U7,U10","74LS161","http://www.ti.com/lit/gpn/sn74LS161","Package_SO:SO-16_3.9x9.9mm_P1.27mm","6",""
"U8,U9","GAL22V10","","Package_DIP:DIP-24_W10.16mm_Socket","2",""
"U15","74LS32","http://www.ti.com/lit/gpn/sn74LS32","Package_SO:SO-14_3.9x8.65mm_P1.27mm","1",""
"U16","74LS08","http://www.ti.com/lit/gpn/sn74LS08","Package_SO:SO-14_3.9x8.65mm_P1.27mm","1",""
"U17","74HC00","http://www.ti.com/lit/gpn/sn74hc00","Package_SO:SO-14_3.9x8.65mm_P1.27mm","1",""
"U19","74HC14","http://www.ti.com/lit/gpn/sn74HC14","Package_SO:SO-14_3.9x8.65mm_P1.27mm","1",""
"X1","TCXO-14","http://www.golledge.com/pdf/products/tcxos/gtxos14.pdf","Oscillator:Oscillator_DIP-14","1",""

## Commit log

2024-11-08 add shield design, timings doc
2024-11-14 added documentation. gerber of v1.0.0
2024-11-14 move readme
2024-11-14 fix table in doc
2024-11-15 fix readme table
2024-12-05 v1.12
2024-12-06 new shield v1.1
2024-12-11 kicad design changes
2025-07-15 working atf1504 vga counter
2025-07-16 double buffer v1
2025-07-16 cleaup
2025-07-17 remove second vga resistor network
2025-07-24 updates to double buffer and multiplexed, 2xatf1508 concept
